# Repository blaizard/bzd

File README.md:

# bzd Framework

Access the [rendered version of this documentation](https://blaizard.github.io/bzd).

Fullstack, lightweight and flexible framework for IoT applications.
This mono-repository enables the following technologies:

|             C++20              |           Rust (2024)           |            Python 3.13            |           Node (v23)            |              Vue               |              Bazel               |              KiCad               |
| :----------------------------: | :-----------------------------: | :-------------------------------: | :-----------------------------: | :----------------------------: | :------------------------------: | :------------------------------: |
|  |  |  |  |  |  |  |

## Overview

This framework is built to run on all sorts of embedded platforms, from bare-metal 8-bit microcontrollers to high-performance compute units.
It is made to remove any dependency on the STL, but to provide a similar set of components and utilities to develop applications in an
efficient and safe manner.

It features the following:

- No dynamic allocations. All storage is declared either at compile time or on the stack.
- The core library is self-contained, with no reliance on third-party libraries, only on the freestanding C++ standard library.
- Flexible error handling model.
- Based on C++ coroutines.
- Compile-time string formatting tool.
- Lightweight.
- Useful set of containers.

## Platforms

The following target platforms are currently supported:

| Name                   | Compiler | Version | Executors   | Debug |
| ---------------------- | -------- | ------- | ----------- | ----- |
| linux_x86_64_clang\*   | clang    | 19.1.7  | host\*      |       |
| linux_x86_64_gcc       | gcc      | 14.2.0  | host\*      |       |
| esp32_xtensa_lx6_gcc   | gcc      | 14.2.0  | sim\*, uart | x     |
| esp32s3_xtensa_lx7_gcc | gcc      | 14.2.0  | sim\*, uart | x     |

\* Default.

When debug is supported by the platform, one can run a target with the `--config=debug` option and a debug environment will
be made available.

## Build

### Locally

To build everything, just run:

```bash
./tools/bazel test //...
```

This will build locally; it will fetch all tools needed to build on your machine.

### Remote

To build Bazel targets, simply run `./tools/bazel` with `--config=remote` appended.

For debugging purposes, toolchains can be run locally in a docker sandbox which is very similar to what runs on remote execution.
To enable this configuration, run `./tools/bazel` with `--config=docker`.

## Documentation

To build the full project documentation, run:

```bash
./tools/bazel run //docs
```

## Code Quality

All supported languages come with their own set of code quality related tools.
To run all static sanity checks, code formatters and documentation generators at once, run the following command:

```bash
./tools/bazel run //:sanitizer
```

To run all tests, run the following command:

```bash
./quality_gate
```

This is a non-exhaustive list of languages and their supported tools. In addition to that,
formatters and linters for YAML, JSON and Markdown are also available.

| Language | Formatters   | Code Analyzers                      | Code Coverage | Test Framework | Documentation |
| -------- | ------------ | ----------------------------------- | ------------- | -------------- | ------------- |
| C++      | clang-format | clang-tidy, asan, lsan, tsan, ubsan | Yes           | Yes            | doxygen-based |
| Python   | ruff         | ruff, mypy                          | Yes           | Yes            |               |
| Node     | prettier     | eslint                              | Yes           | Yes            |               |
| Skylark  | buildifier   | buildifier                          |               |                | stardoc       |

Update `compile_commands.json`

```bash
./tools/bazel run @bzd_sanitizer//aspects/compile_commands:build
```

Update `rust-project.json`

```bash
./tools/bazel run @rules_rust//tools/rust_analyzer:gen_rust_project -- //rust/...
```

## Naming Convention

The code in this repository follows several principles regarding naming conventions. The following rules are applied across languages.

- Files and directories are named lower case `snake_case` using only the characters matching the regex: `[a-z0-9_/.]`. This is enforced by tools/bazel_build/modules/bzd_sanitizer/actions/structure.
- Variables, constants, functions, concepts, namespaces are named in `camelCase`.
- All types are named in `PascalCase`.
- Non-public members (variables, functions...) are appended with a `_` character.
- All names avoid abbreviations.

## Memory Footprint

All classes offered by this library share the same objective: a fixed memory size. Their footprint or maximum size
is determined at compile time, ensuring no memory allocation at runtime, making this library ideal for any safety-critical application.

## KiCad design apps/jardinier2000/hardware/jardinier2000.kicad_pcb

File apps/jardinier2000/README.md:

# Jardinier2000

## Software

::: //apps/jardinier2000:diagram

### Program

```bash
./tools/bazel run //apps/jardinier2000:jardinier2000.platform --config=esp32s3 --run_under=@bzd_espressif//runner/esp32s3:uart --config=prod
```

## Hardware

- v0.1: a6dc53e17e0d28d296f038ecd4dc024c1fd0ac4c
- v0.2: 74176779d8ccca15caded8594085d71fdf246d6d
- v0.3: (wip)
  - Step down:
    - Updated coil 3.3uH 6x6mm -> 4.7uH 8x8mm.
    - Adding C21 & C22 at VIN to damp voltage spikes.
  - Moved SW1 from IO45 -> IO47 (IO45 is a special pin).
  - Reset capacitor (C6) 0.1uF -> 1uF as recommended by Espressif.

TODO: 3.3V LDO Dropout Voltage Margin (U2 - NCP1117-3.3)

- Issue: The 3.3V rail uses an NCP1117-3.3 LDO (U2), which has a high dropout voltage ($V_{DO} \approx 1.0\text{V} - 1.2\text{V}$). The LDO input is supplied from 5V through Schottky diodes D1 or D7 ($\Delta V \approx 0.4\text{V}$), leaving $V_{IN} \approx 4.6\text{V}$.
- Risk: If powered via USB-C and the cable voltage sags slightly (e.g., to 4.75V), $V_{IN}$ to the LDO drops to ~4.35V. This falls below the minimum required input voltage ($3.3\text{V} + 1.1\text{V} = 4.4\text{V}$), potentially causing 3.3V brownouts during ESP32-S3 Wi-Fi TX current spikes.
- Fix: Replace U2 with a lower-dropout LDO (e.g., AP2112K-3.3 or TLV1117LV33, both with $V_{DO} \le 0.4\text{V}$).

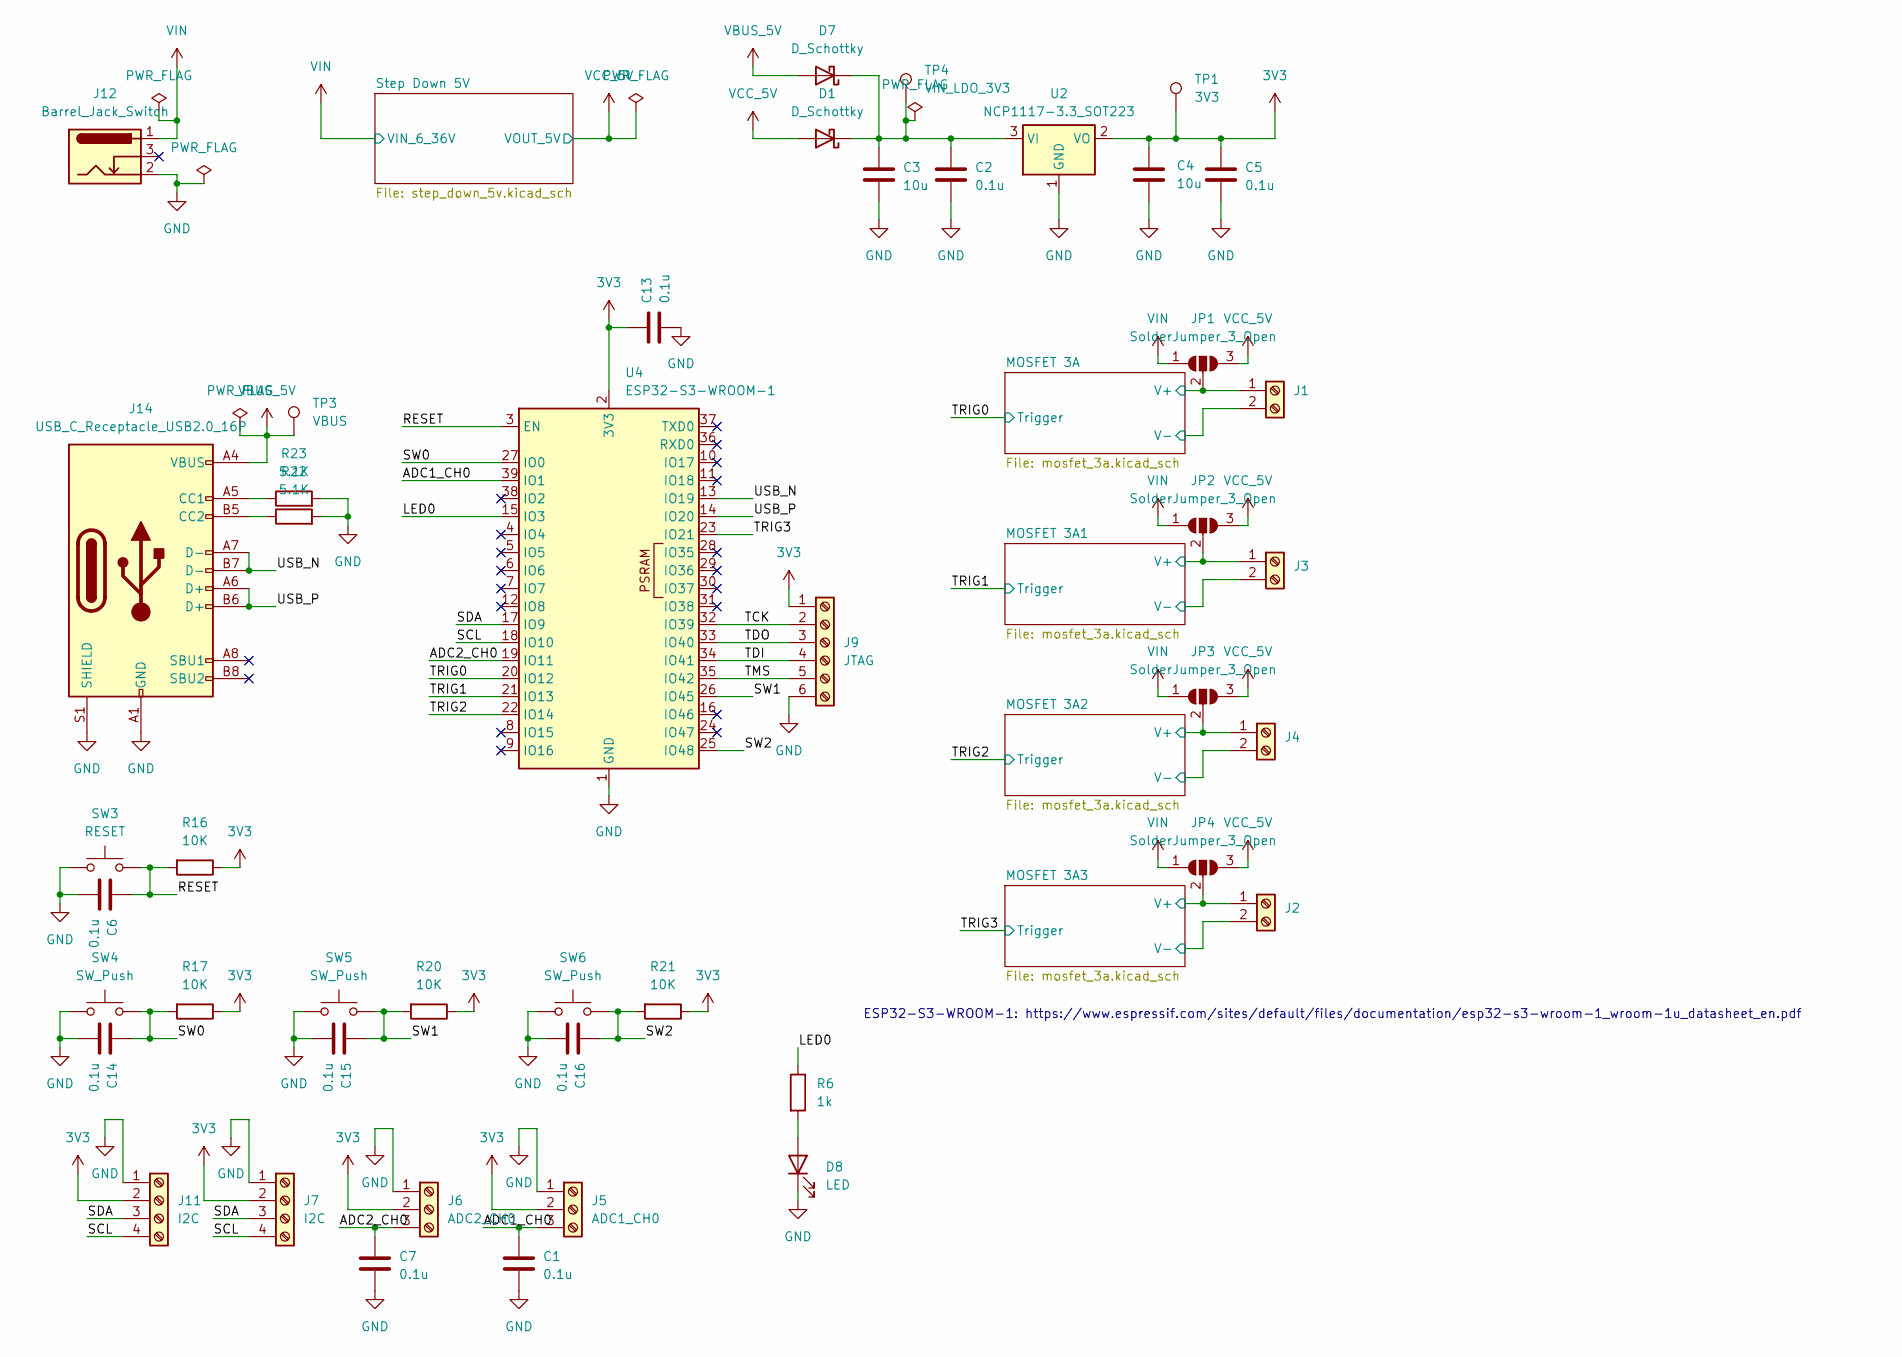
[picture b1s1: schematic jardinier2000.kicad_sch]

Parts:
C1, C2, C5, C6, C7, C13, C14, C15, C16: 0.1u; C_0805_2012Metric_Pad1.18x1.45mm_HandSolder
C3, C4: 10u; C_0805_2012Metric_Pad1.18x1.45mm_HandSolder
D1, D7: D_Schottky; D_0805_2012Metric_Pad1.15x1.40mm_HandSolder
D8: LED; LED_0805_2012Metric_Pad1.15x1.40mm_HandSolder
J1, J2, J3, J4: TerminalBlock_Phoenix_MKDS-1,5-2-5.08_1x02_P5.08mm_Horizont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
J5: ADC1_CH0; JST_XH_B3B-XH-AM_1x03_P2.50mm_Vertical
J6: ADC2_CH0; JST_XH_B3B-XH-AM_1x03_P2.50mm_Vertical
J7, J11: I2C; JST_XH_B4B-XH-AM_1x04_P2.50mm_Vertical
J9: JTAG; JST_XH_B6B-XH-AM_1x06_P2.50mm_Vertical
J12: Barrel_Jack_Switch; BarrelJack_Horizontal
J14: USB_C_Receptacle_USB2.0_16P; USB_C_Receptacle_G-Switch_GT-USB-7010ASV
JP1, JP2, JP3, JP4: SolderJumper_3_Open; SolderJumper-3_P1.3mm_Open_Pad1.0x1.5mm_NumberLabels
R6: 1k; R_0805_2012Metric_Pad1.20x1.40mm_HandSolder
R16, R17, R20, R21: 10K; R_0805_2012Metric_Pad1.20x1.40mm_HandSolder
R22, R23: 5.1K; R_0805_2012Metric_Pad1.20x1.40mm_HandSolder
SW3: RESET; push_button_6x3
SW4, SW5, SW6: SW_Push; SW_PUSH_6mm
TP1: 3V3; TestPoint_Pad_2.0x2.0mm
TP3: VBUS; TestPoint_Pad_2.0x2.0mm
TP4: VIN_LDO_3V3; TestPoint_Pad_2.0x2.0mm
U2: NCP1117-3.3_SOT223; SOT-223-3_TabPin2
U4: ESP32-S3-WROOM-1

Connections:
3V3: C4.1, C5.1, C13.1, J5.2, J6.2, J7.2, J9.1, J11.2, R16.1, R17.1, R20.1, R21.1, TP1.1, U2.2 (VO), U4.2 (3V3)
/ADC1_CH0: C1.1, J5.3, U4.39 (IO1)
/ADC2_CH0: C7.1, J6.3, U4.19 (IO11)
/LED0: R6.1, U4.15 (IO3)
/MOSFET 3A1/V+: J3.1, JP2.2 (C); also elsewhere on the board
/MOSFET 3A1/V-: J3.2; also elsewhere on the board
/MOSFET 3A2/V+: J4.1, JP3.2 (C); also elsewhere on the board
/MOSFET 3A2/V-: J4.2; also elsewhere on the board
/MOSFET 3A3/V+: J2.1, JP4.2 (C); also elsewhere on the board
/MOSFET 3A3/V-: J2.2; also elsewhere on the board
/MOSFET 3A/V+: J1.1, JP1.2 (C); also elsewhere on the board
/MOSFET 3A/V-: J1.2; also elsewhere on the board
/RESET: C6.1, R16.2, SW3.2, U4.3 (EN)
/SCL: J7.4, J11.4, U4.18 (IO10)
/SDA: J7.3, J11.3, U4.17 (IO9)
/SW0: C14.1, R17.2, SW4.2, U4.27 (IO0)
/SW1: C15.1, R20.2, SW5.2, U4.26 (IO45)
/SW2: C16.1, R21.2, SW6.2, U4.25 (IO48)
/TCK: J9.2, U4.32 (IO39)
/TDI: J9.4, U4.34 (IO41)
/TDO: J9.3, U4.33 (IO40)
/TMS: J9.5, U4.35 (IO42)
/TRIG0: U4.20 (IO12); also elsewhere on the board
/TRIG1: U4.21 (IO13); also elsewhere on the board
/TRIG2: U4.22 (IO14); also elsewhere on the board
/TRIG3: U4.23 (IO21); also elsewhere on the board
/USB_N: J14.A7 (D-), J14.B7 (D-), U4.13 (IO19)
/USB_P: J14.A6 (D+), J14.B6 (D+), U4.14 (IO20)
GND: C1.2, C2.2, C3.2, C4.2, C5.2, C6.2, C7.2, C13.2, C14.2, C15.2, C16.2, D8.1 (K), J5.1, J6.1, J7.1, J9.6, J11.1, J12.2, J14.A1 (GND), J14.A12 (GND), J14.B1 (GND), J14.B12 (GND), J14.S1 (SHIELD), R22.2, R23.2, SW3.1, SW4.1, SW5.1, SW6.1, U2.1 (GND), U4.1 (GND), U4.40 (GND), U4.41 (GND); also elsewhere on the board
unnamed: C2.1, C3.1, D1.1 (K), D7.1 (K), TP4.1, U2.3 (VI)
unnamed: D8.2 (A), R6.2
unnamed: J14.A5 (CC1), R23.1
unnamed: J14.B5 (CC2), R22.1
VBUS_5V: D7.2 (A), J14.A4 (VBUS), J14.A9 (VBUS), J14.B4 (VBUS), J14.B9 (VBUS), TP3.1
VCC_5V: D1.2 (A), JP1.3 (B), JP2.3 (B), JP3.3 (B), JP4.3 (B); also elsewhere on the board
VIN: J12.1, JP1.1 (A), JP2.1 (A), JP3.1 (A), JP4.1 (A); also elsewhere on the board

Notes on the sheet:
ESP32-S3-WROOM-1: https://www.espressif.com/sites/default/files/documentation/esp32-s3-wroom-1_wroom-1u_datasheet_en.pdf

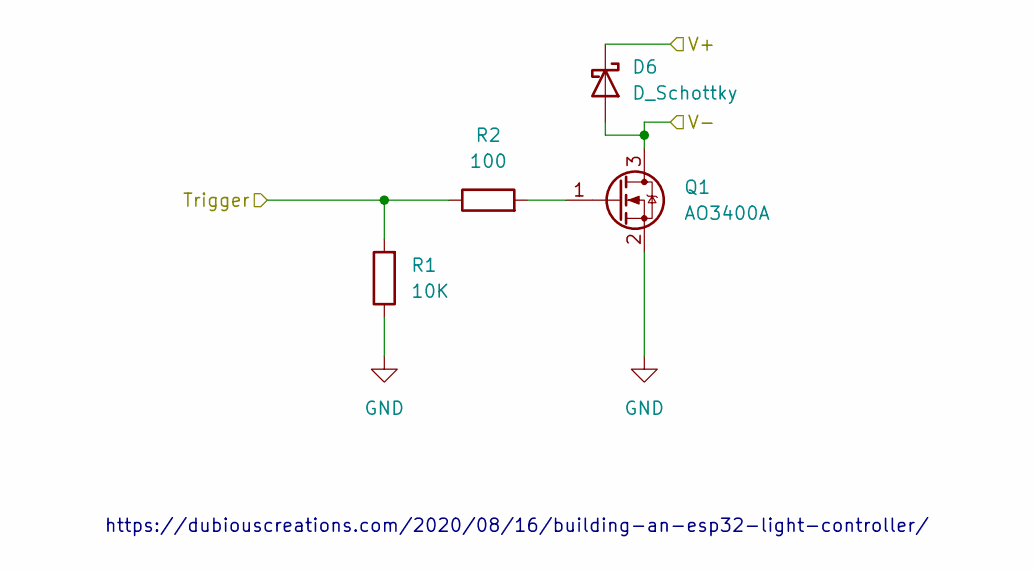
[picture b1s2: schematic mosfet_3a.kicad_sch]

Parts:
D6: D_Schottky; D_0805_2012Metric_Pad1.15x1.40mm_HandSolder
Q1: AO3400A; SOT-23
R1: 10K; R_0805_2012Metric_Pad1.20x1.40mm_HandSolder
R2: 100; R_0805_2012Metric_Pad1.20x1.40mm_HandSolder

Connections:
/MOSFET 3A/V+: D6.1 (K); also elsewhere on the board
/MOSFET 3A/V-: D6.2 (A), Q1.3 (D); also elsewhere on the board
/TRIG0: R1.2, R2.1; also elsewhere on the board
GND: Q1.2 (S), R1.1; also elsewhere on the board
unnamed: Q1.1 (G), R2.2

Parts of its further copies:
D2, D3, D4: D_Schottky; D_0805_2012Metric_Pad1.15x1.40mm_HandSolder
Q2, Q3, Q4: AO3400A; SOT-23
R3, R5, R7: 10K; R_0805_2012Metric_Pad1.20x1.40mm_HandSolder
R4, R8, R9: 100; R_0805_2012Metric_Pad1.20x1.40mm_HandSolder

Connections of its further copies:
/MOSFET 3A1/V+: D2.1 (K); also elsewhere on the board
/MOSFET 3A1/V-: D2.2 (A), Q2.3 (D); also elsewhere on the board
/MOSFET 3A2/V+: D3.1 (K); also elsewhere on the board
/MOSFET 3A2/V-: D3.2 (A), Q3.3 (D); also elsewhere on the board
/MOSFET 3A3/V+: D4.1 (K); also elsewhere on the board
/MOSFET 3A3/V-: D4.2 (A), Q4.3 (D); also elsewhere on the board
/TRIG1: R3.2, R4.1; also elsewhere on the board
/TRIG2: R5.2, R9.1; also elsewhere on the board
/TRIG3: R7.2, R8.1; also elsewhere on the board
GND: Q2.2 (S), Q3.2 (S), Q4.2 (S), R3.1, R5.1, R7.1; also elsewhere on the board
unnamed: Q2.1 (G), R4.2
unnamed: Q3.1 (G), R9.2
unnamed: Q4.1 (G), R8.2

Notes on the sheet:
https://dubiouscreations.com/2020/08/16/building-an-esp32-light-controller/

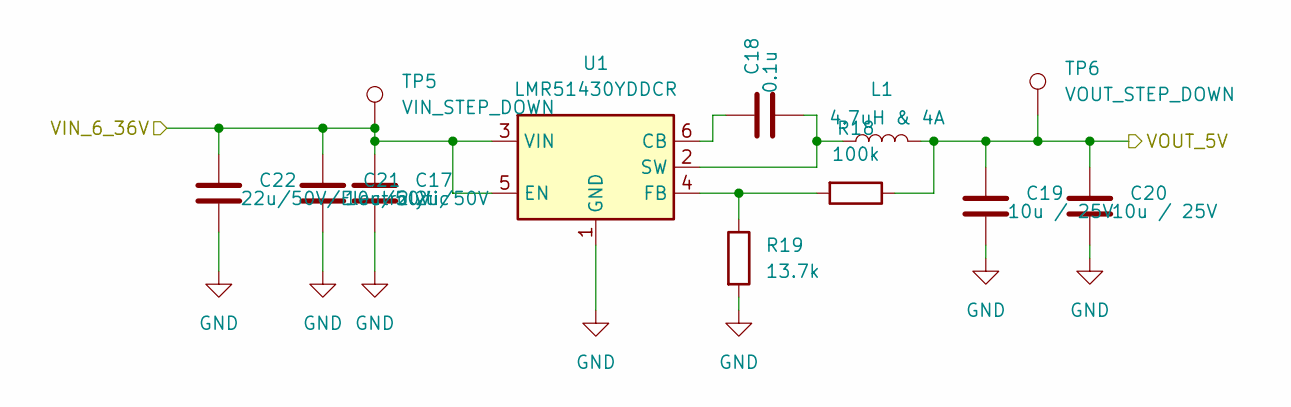
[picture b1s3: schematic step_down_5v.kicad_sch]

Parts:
C17: 2.2u/50V; C_0805_2012Metric_Pad1.18x1.45mm_HandSolder
C18: 0.1u; C_0805_2012Metric_Pad1.18x1.45mm_HandSolder
C19, C20: 10u / 25V; C_0805_2012Metric_Pad1.18x1.45mm_HandSolder
C21: 10u/50V; C_0805_2012Metric_Pad1.18x1.45mm_HandSolder
C22: 22u/50V/Electrolytic; CP_Radial_D4.0mm_P1.50mm
L1: 4.7uH & 4A; L_Cenker_CKCS8060
R18: 100k; R_0805_2012Metric_Pad1.20x1.40mm_HandSolder
R19: 13.7k; R_0805_2012Metric_Pad1.20x1.40mm_HandSolder
TP5: VIN_STEP_DOWN; TestPoint_Pad_2.0x2.0mm
TP6: VOUT_STEP_DOWN; TestPoint_Pad_2.0x2.0mm
U1: LMR51430YDDCR; SOT-23-6

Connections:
GND: C17.2, C19.2, C20.2, C21.2, C22.2, R19.2, U1.1 (GND); also elsewhere on the board
unnamed: C18.1, U1.6 (CB)
unnamed: R18.2, R19.1, U1.4 (FB)
unnamed: C18.2, L1.1, U1.2 (SW)
VCC_5V: C19.1, C20.1, L1.2, R18.1, TP6.1; also elsewhere on the board
VIN: C17.1, C21.1, C22.1, TP5.1, U1.3 (VIN), U1.5 (EN); also elsewhere on the board

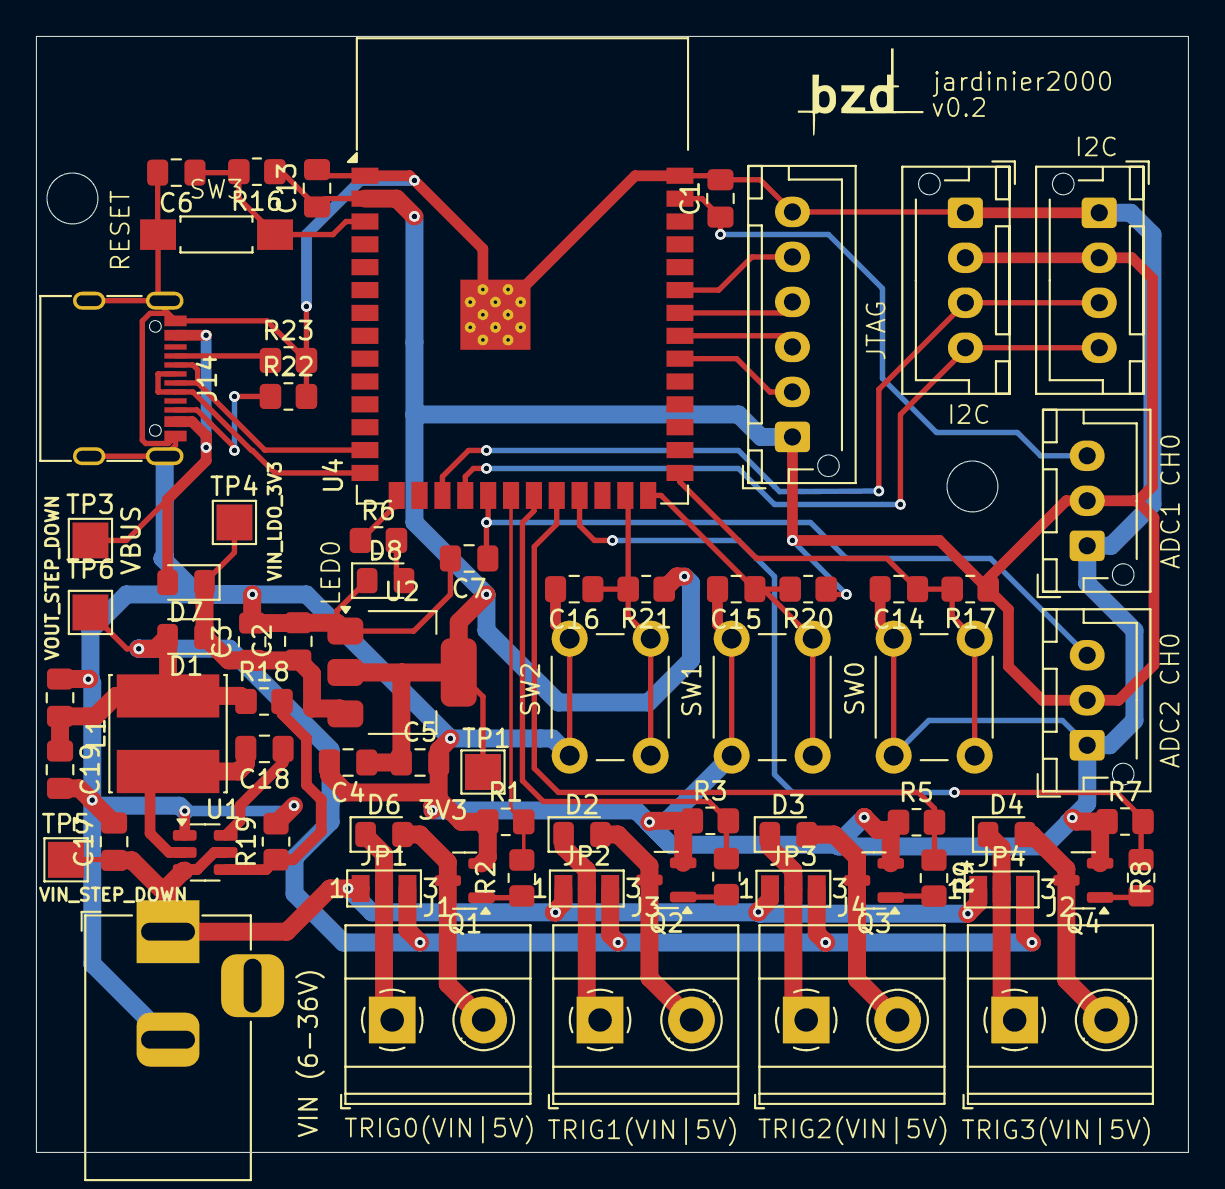
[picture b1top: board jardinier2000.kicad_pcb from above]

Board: 2 copper layers, 64.0 x 62.0 mm, 71 parts (0 on the bottom side), 43 nets.
